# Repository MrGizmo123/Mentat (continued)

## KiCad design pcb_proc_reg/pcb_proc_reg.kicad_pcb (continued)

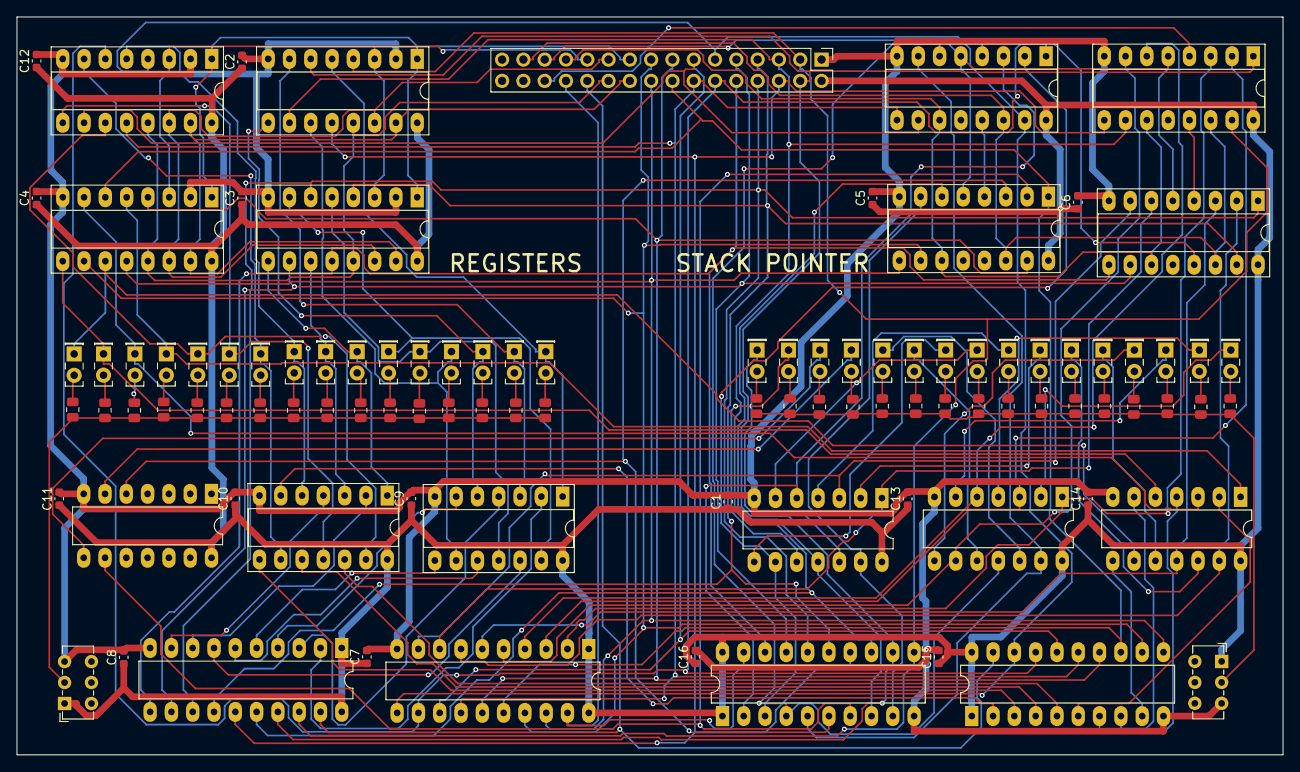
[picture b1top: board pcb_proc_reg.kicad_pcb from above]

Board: 2 copper layers, 151.0 x 88.0 mm, 101 parts (0 on the bottom side), 130 nets.

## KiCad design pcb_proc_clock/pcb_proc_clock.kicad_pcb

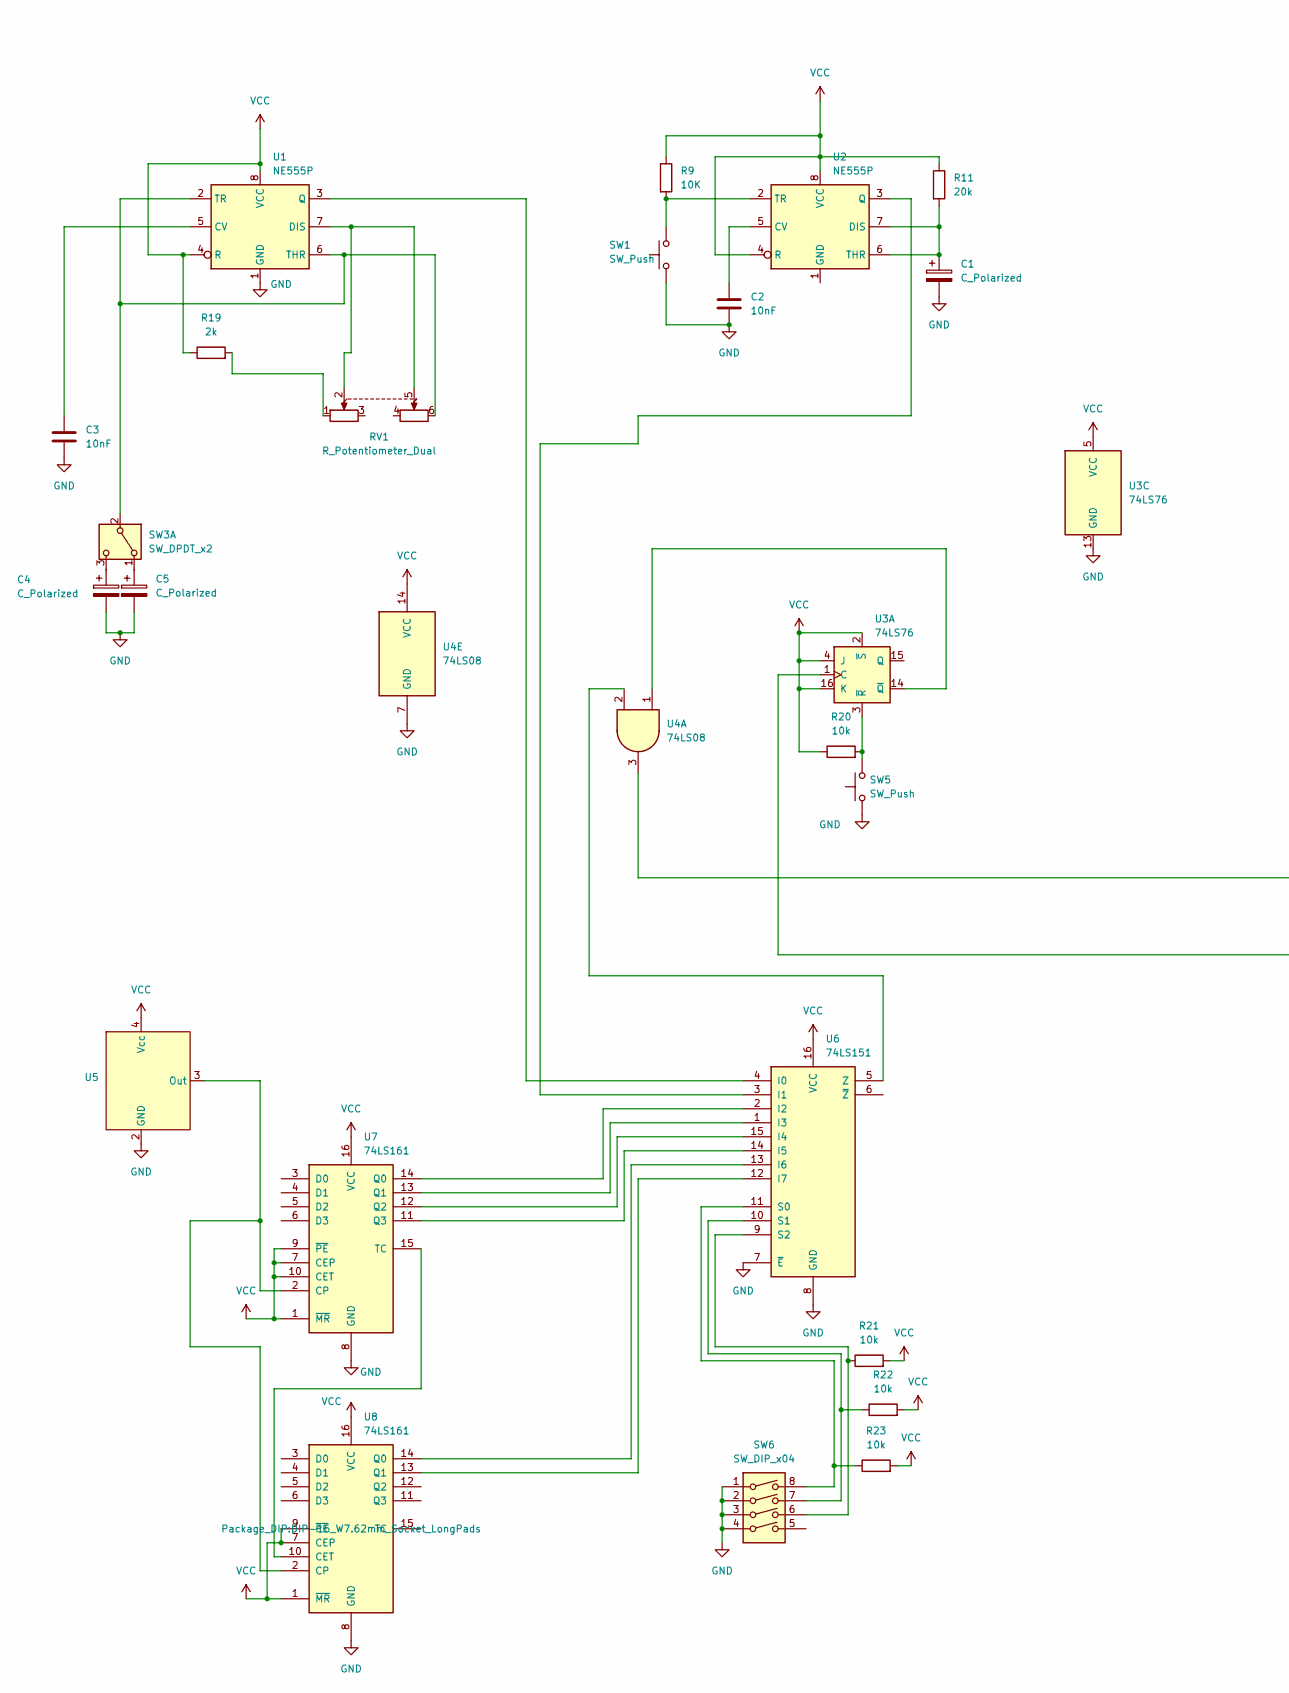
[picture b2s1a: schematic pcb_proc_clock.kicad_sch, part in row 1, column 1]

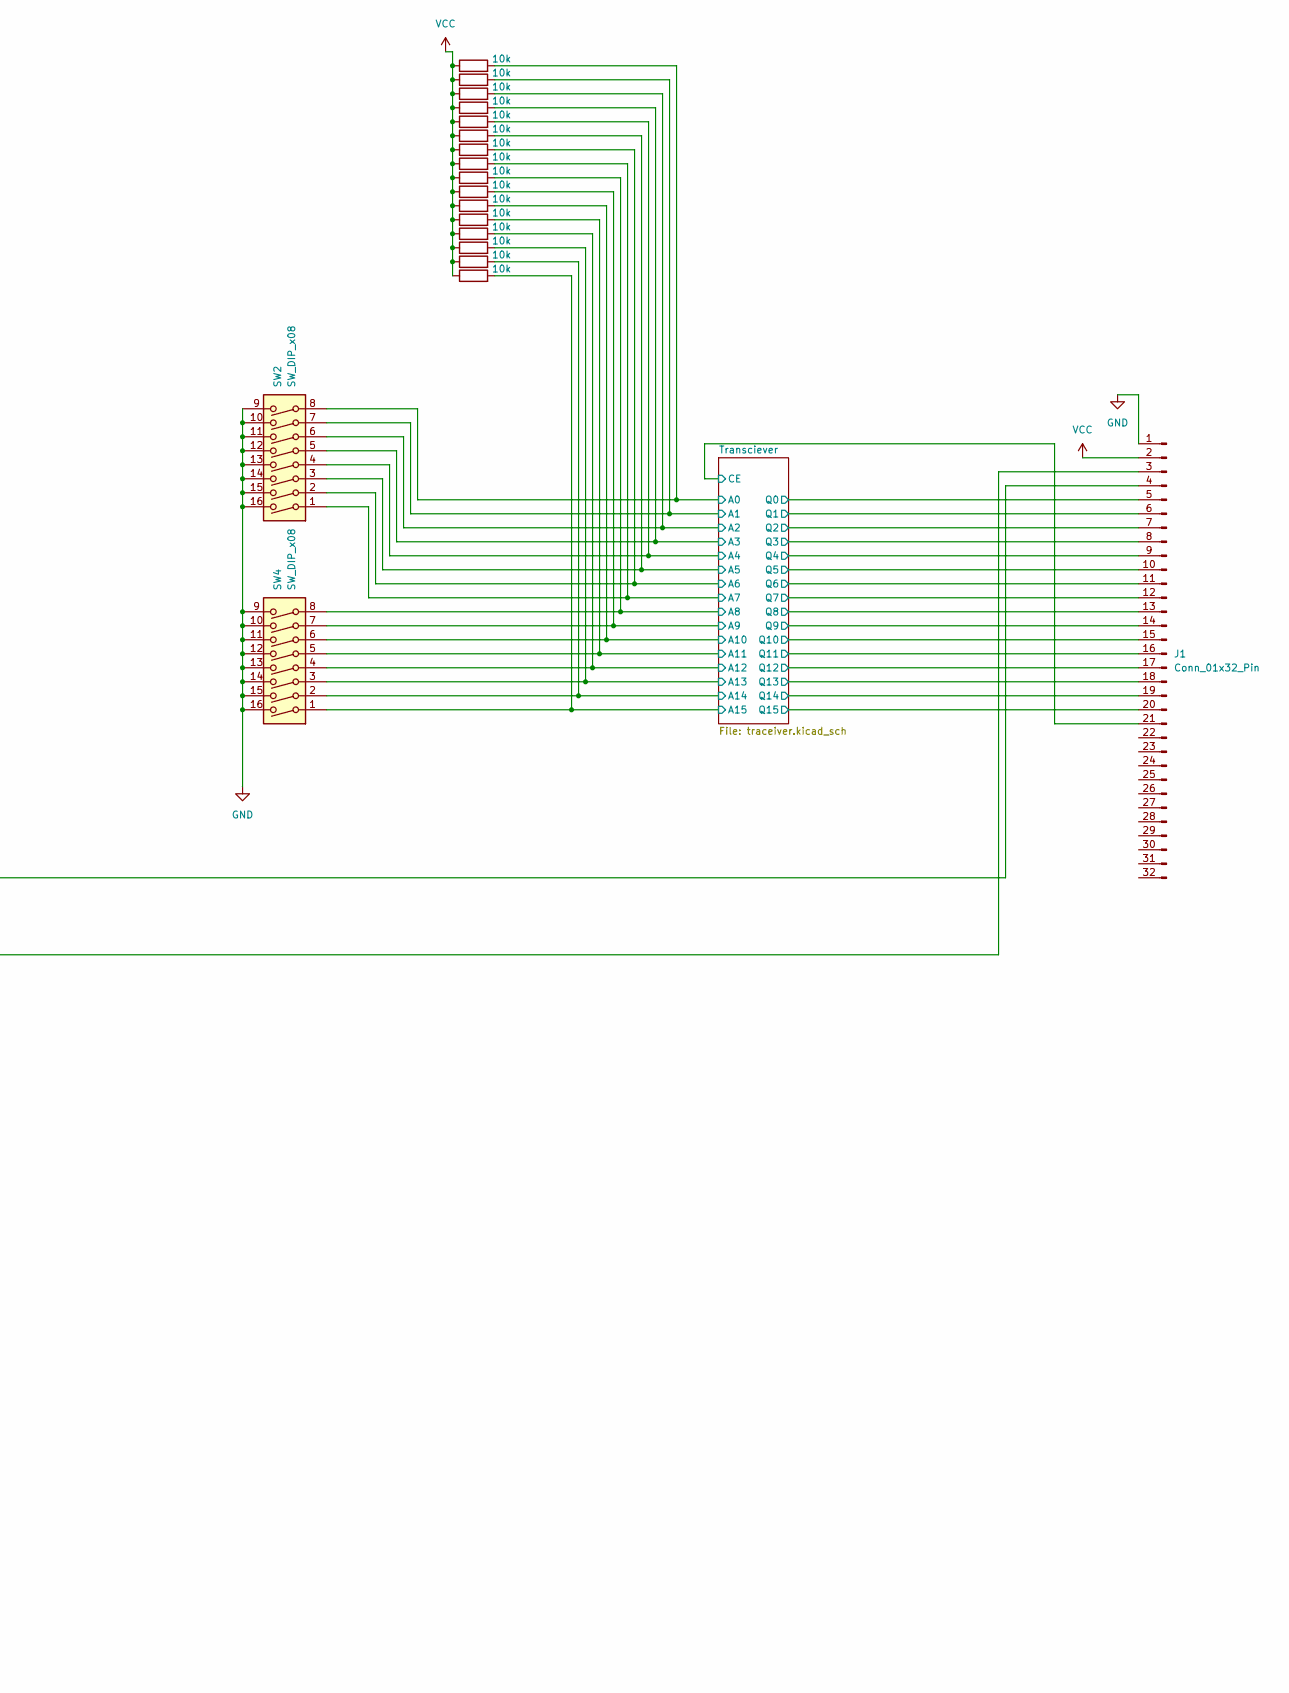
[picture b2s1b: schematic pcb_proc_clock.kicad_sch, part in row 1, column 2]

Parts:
C1, C4, C5: C_Polarized; CP_Radial_D4.0mm_P1.50mm
C2, C3: 10nF; C_Disc_D3.0mm_W1.6mm_P2.50mm
J1: Conn_01x32_Pin; PinHeader_2x16_P2.54mm_Vertical
R1, R2, R3, R4, R5, R6, R7, R8, R10, R12, R13, R14, R15, R16, R17, R18, R20, R21, R22, R23: 10k; R_0805_2012Metric
R9: 10K; R_0805_2012Metric
R11: 20k; R_0805_2012Metric
R19: 2k; R_0805_2012Metric
RV1: R_Potentiometer_Dual; Potentiometer_Alps_RK163_Dual_Horizontal
SW1, SW5: SW_Push; SW_PUSH_6mm
SW2, SW4: SW_DIP_x08; SW_DIP_SPSTx08_Slide_9.78x22.5mm_W7.62mm_P2.54mm
SW3: SW_DPDT_x2; SW_CK_JS202011CQN_DPDT_Straight
SW6: SW_DIP_x04; DIP-8_W7.62mm_LongPads
U1, U2: NE555P; DIP-8_W7.62mm_Socket_LongPads
U3: 74LS76; DIP-16_W7.62mm_Socket_LongPads
U4: 74LS08; DIP-14_W7.62mm_Socket_LongPads
U5: MCO-1510A
U6: 74LS151; DIP-16_W7.62mm_Socket_LongPads
U7, U8: 74LS161; DIP-16_W7.62mm_Socket_LongPads

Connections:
/Transciever/A0: R1.2, SW2.8; also elsewhere on the board
/Transciever/A1: R2.2, SW2.7; also elsewhere on the board
/Transciever/A2: R3.2, SW2.6; also elsewhere on the board
/Transciever/A3: R4.2, SW2.5; also elsewhere on the board
/Transciever/A4: R5.2, SW2.4; also elsewhere on the board
/Transciever/A5: R6.2, SW2.3; also elsewhere on the board
/Transciever/A6: R7.2, SW2.2; also elsewhere on the board
/Transciever/A7: R8.2, SW2.1; also elsewhere on the board
/Transciever/A8: R10.2, SW4.8; also elsewhere on the board
/Transciever/A9: R12.2, SW4.7; also elsewhere on the board
/Transciever/A10: R13.2, SW4.6; also elsewhere on the board
/Transciever/A11: R14.2, SW4.5; also elsewhere on the board
/Transciever/A12: R15.2, SW4.4; also elsewhere on the board
/Transciever/A13: R16.2, SW4.3; also elsewhere on the board
/Transciever/A14: R17.2, SW4.2; also elsewhere on the board
/Transciever/A15: R18.2, SW4.1; also elsewhere on the board
/Transciever/CE: J1.21; also elsewhere on the board
/Transciever/Q0: J1.5; also elsewhere on the board
/Transciever/Q1: J1.6; also elsewhere on the board
/Transciever/Q2: J1.7; also elsewhere on the board
/Transciever/Q3: J1.8; also elsewhere on the board
/Transciever/Q4: J1.9; also elsewhere on the board
/Transciever/Q5: J1.10; also elsewhere on the board
/Transciever/Q6: J1.11; also elsewhere on the board
/Transciever/Q7: J1.12; also elsewhere on the board
/Transciever/Q8: J1.13; also elsewhere on the board
/Transciever/Q9: J1.14; also elsewhere on the board
/Transciever/Q10: J1.15; also elsewhere on the board
/Transciever/Q11: J1.16; also elsewhere on the board
/Transciever/Q12: J1.17; also elsewhere on the board
/Transciever/Q13: J1.18; also elsewhere on the board
/Transciever/Q14: J1.19; also elsewhere on the board
/Transciever/Q15: J1.20; also elsewhere on the board
GND: C1.2, C2.2, C3.2, C4.2, C5.2, J1.1, SW1.1, SW2.9, SW2.10, SW2.11, SW2.12, SW2.13, SW2.14, SW2.15, SW2.16, SW4.9, SW4.10, SW4.11, SW4.12, SW4.13, SW4.14, SW4.15, SW4.16, SW5.1, SW6.1, SW6.2, SW6.3, SW6.4, U1.1 (GND), U3.13 (GND), U4.7 (GND), U5.2 (GND), U6.7 (~E), U6.8 (GND), U7.8 (GND), U8.8 (GND); also elsewhere on the board
unnamed: J1.3, U3.1 (C)
unnamed: J1.4, U4.3
unnamed: R19.2, RV1.1
unnamed: C5.1, SW3.1 (A)
unnamed: RV1.6, SW3.2 (B), U1.2 (TR), U1.6 (THR)
unnamed: C4.1, SW3.3 (C)
unnamed: C3.1, U1.5 (CV)
unnamed: RV1.2, RV1.5, U1.7 (DIS)
unnamed: U1.3 (Q), U6.4 (I0)
unnamed: C2.1, U2.5 (CV)
unnamed: C1.1, R11.2, U2.6 (THR), U2.7 (DIS)
unnamed: U2.3 (Q), U6.3 (I1)
unnamed: R9.2, SW1.2, U2.2 (TR)
unnamed: U3.14 (~Q), U4.1
unnamed: R20.2, SW5.2, U3.3 (~R)
unnamed: U5.3 (Out), U7.2 (CP), U8.2 (CP)
unnamed: U6.2 (I2), U7.14 (Q0)
unnamed: U6.1 (I3), U7.13 (Q1)
unnamed: U6.15 (I4), U7.12 (Q2)
unnamed: U6.14 (I5), U7.11 (Q3)
unnamed: U6.13 (I6), U8.14 (Q0)
unnamed: U6.12 (I7), U8.13 (Q1)
unnamed: R23.1, SW6.8, U6.11 (S0)
unnamed: R22.1, SW6.7, U6.10 (S1)
unnamed: R21.1, SW6.6, U6.9 (S2)
unnamed: U4.2, U6.5 (Z)
unnamed: U7.15 (TC), U8.10 (CET)
VCC: J1.2, R1.1, R2.1, R3.1, R4.1, R5.1, R6.1, R7.1, R8.1, R9.1, R10.1, R11.1, R12.1, R13.1, R14.1, R15.1, R16.1, R17.1, R18.1, R19.1, R20.1, R21.2, R22.2, R23.2, U1.4 (R), U1.8 (VCC), U2.4 (R), U2.8 (VCC), U3.2 (~S), U3.4 (J), U3.5 (VCC), U3.16 (K), U4.14 (VCC), U5.4 (Vcc), U6.16 (VCC), U7.1 (~MR), U7.7 (CEP), U7.9 (~PE), U7.10 (CET), U7.16 (VCC), U8.1 (~MR), U8.7 (CEP), U8.9 (~PE), U8.16 (VCC); also elsewhere on the board

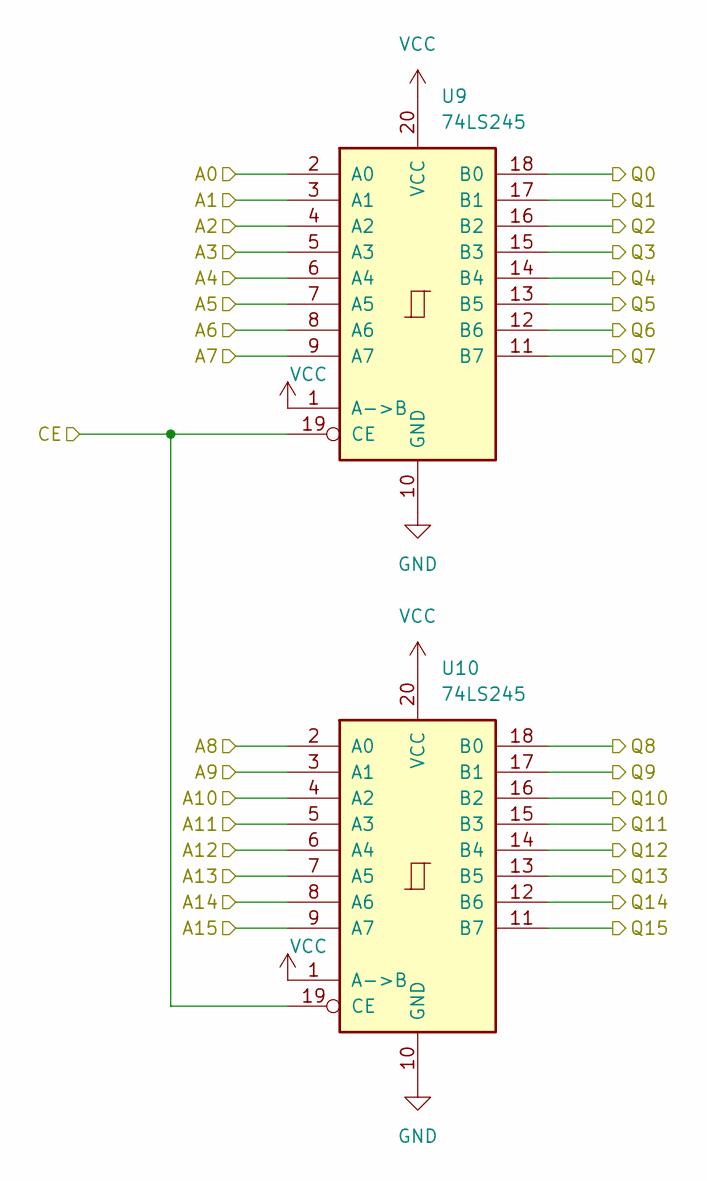
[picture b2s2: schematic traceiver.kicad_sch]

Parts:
U9, U10: 74LS245; DIP-20_W7.62mm_LongPads

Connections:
/Transciever/A0: U9.2 (A0); also elsewhere on the board
/Transciever/A1: U9.3 (A1); also elsewhere on the board
/Transciever/A2: U9.4 (A2); also elsewhere on the board
/Transciever/A3: U9.5 (A3); also elsewhere on the board
/Transciever/A4: U9.6 (A4); also elsewhere on the board
/Transciever/A5: U9.7 (A5); also elsewhere on the board
/Transciever/A6: U9.8 (A6); also elsewhere on the board
/Transciever/A7: U9.9 (A7); also elsewhere on the board
/Transciever/A8: U10.2 (A0); also elsewhere on the board
/Transciever/A9: U10.3 (A1); also elsewhere on the board
/Transciever/A10: U10.4 (A2); also elsewhere on the board
/Transciever/A11: U10.5 (A3); also elsewhere on the board
/Transciever/A12: U10.6 (A4); also elsewhere on the board
/Transciever/A13: U10.7 (A5); also elsewhere on the board
/Transciever/A14: U10.8 (A6); also elsewhere on the board
/Transciever/A15: U10.9 (A7); also elsewhere on the board
/Transciever/CE: U9.19 (CE), U10.19 (CE); also elsewhere on the board
/Transciever/Q0: U9.18 (B0); also elsewhere on the board
/Transciever/Q1: U9.17 (B1); also elsewhere on the board
/Transciever/Q2: U9.16 (B2); also elsewhere on the board
/Transciever/Q3: U9.15 (B3); also elsewhere on the board
/Transciever/Q4: U9.14 (B4); also elsewhere on the board
/Transciever/Q5: U9.13 (B5); also elsewhere on the board
/Transciever/Q6: U9.12 (B6); also elsewhere on the board
/Transciever/Q7: U9.11 (B7); also elsewhere on the board
/Transciever/Q8: U10.18 (B0); also elsewhere on the board
/Transciever/Q9: U10.17 (B1); also elsewhere on the board
/Transciever/Q10: U10.16 (B2); also elsewhere on the board
/Transciever/Q11: U10.15 (B3); also elsewhere on the board
/Transciever/Q12: U10.14 (B4); also elsewhere on the board
/Transciever/Q13: U10.13 (B5); also elsewhere on the board
/Transciever/Q14: U10.12 (B6); also elsewhere on the board
/Transciever/Q15: U10.11 (B7); also elsewhere on the board
GND: U9.10 (GND), U10.10 (GND); also elsewhere on the board
VCC: U9.1 (A->B), U9.20 (VCC), U10.1 (A->B), U10.20 (VCC); also elsewhere on the board

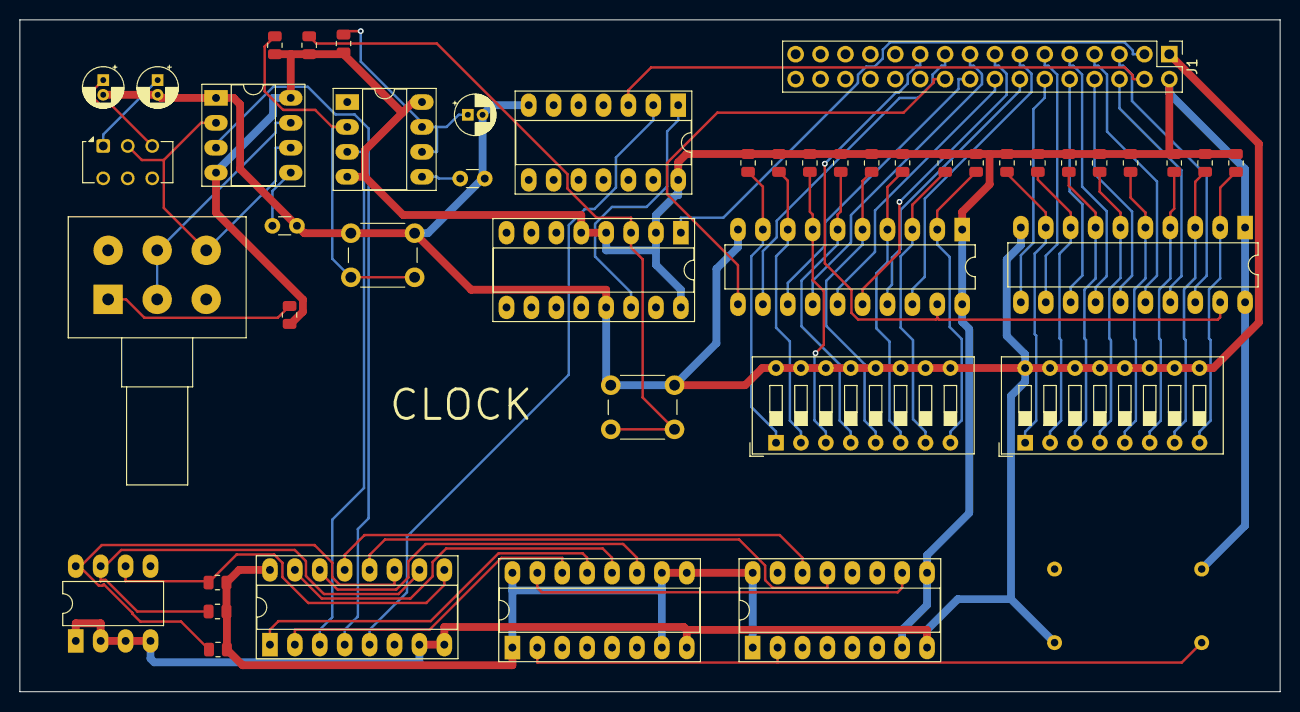
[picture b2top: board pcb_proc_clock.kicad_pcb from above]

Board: 2 copper layers, 128.5 x 68.5 mm, 46 parts (0 on the bottom side), 62 nets.

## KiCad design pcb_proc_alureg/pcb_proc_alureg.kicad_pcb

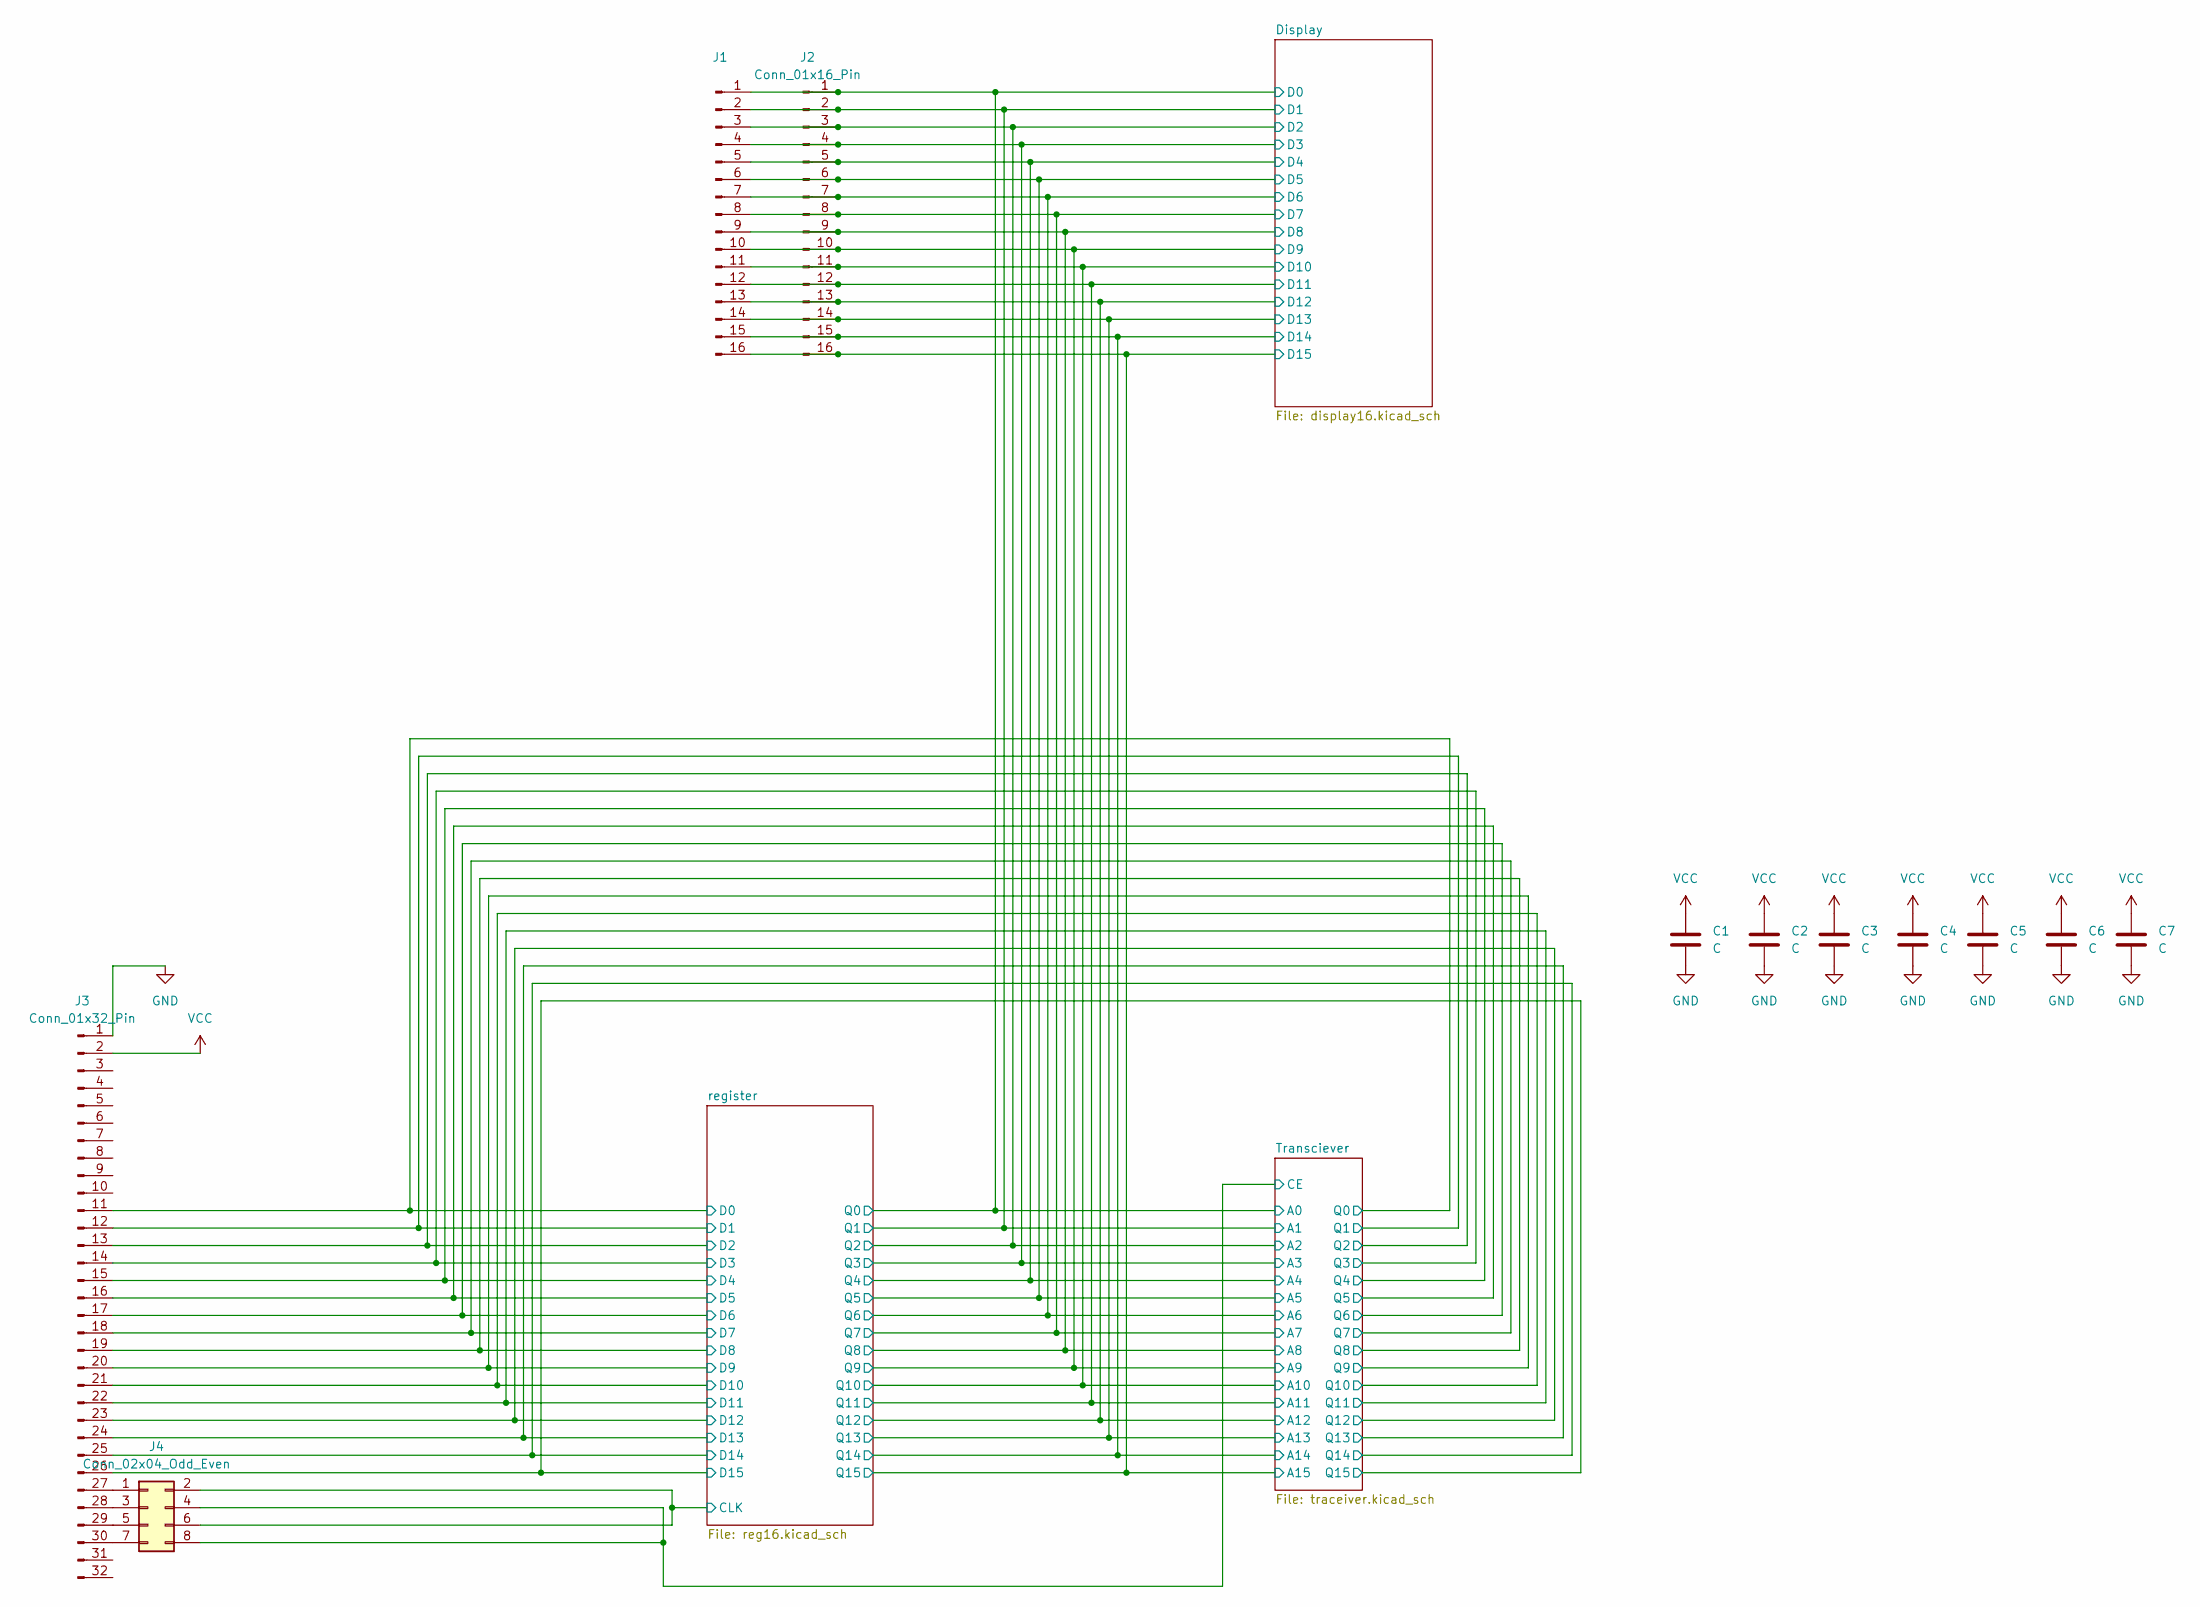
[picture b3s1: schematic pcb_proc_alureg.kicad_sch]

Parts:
C1, C2, C3, C4, C5, C6, C7: C; C_0805_2012Metric
J1, J2: Conn_01x16_Pin; PinSocket_1x16_P2.54mm_Vertical
J3: Conn_01x32_Pin; PinHeader_1x32_P2.54mm_Horizontal
J4: Conn_02x04_Odd_Even; PinSocket_2x04_P2.54mm_Vertical

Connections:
/Display/D0: J1.1, J2.1; also elsewhere on the board
/Display/D1: J1.2, J2.2; also elsewhere on the board
/Display/D2: J1.3, J2.3; also elsewhere on the board
/Display/D3: J1.4, J2.4; also elsewhere on the board
/Display/D4: J1.5, J2.5; also elsewhere on the board
/Display/D5: J1.6, J2.6; also elsewhere on the board
/Display/D6: J1.7, J2.7; also elsewhere on the board
/Display/D7: J1.8, J2.8; also elsewhere on the board
/Display/D8: J1.9, J2.9; also elsewhere on the board
/Display/D9: J1.10, J2.10; also elsewhere on the board
/Display/D10: J1.11, J2.11; also elsewhere on the board
/Display/D11: J1.12, J2.12; also elsewhere on the board
/Display/D12: J1.13, J2.13; also elsewhere on the board
/Display/D13: J1.14, J2.14; also elsewhere on the board
/Display/D14: J1.15, J2.15; also elsewhere on the board
/Display/D15: J1.16, J2.16; also elsewhere on the board
/Transciever/CE: J4.4, J4.8; also elsewhere on the board
/Transciever/Q0: J3.11; also elsewhere on the board
/Transciever/Q1: J3.12; also elsewhere on the board
/Transciever/Q2: J3.13; also elsewhere on the board
/Transciever/Q3: J3.14; also elsewhere on the board
/Transciever/Q4: J3.15; also elsewhere on the board
/Transciever/Q5: J3.16; also elsewhere on the board
/Transciever/Q6: J3.17; also elsewhere on the board
/Transciever/Q7: J3.18; also elsewhere on the board
/Transciever/Q8: J3.19; also elsewhere on the board
/Transciever/Q9: J3.20; also elsewhere on the board
/Transciever/Q10: J3.21; also elsewhere on the board
/Transciever/Q11: J3.22; also elsewhere on the board
/Transciever/Q12: J3.23; also elsewhere on the board
/Transciever/Q13: J3.24; also elsewhere on the board
/Transciever/Q14: J3.25; also elsewhere on the board
/Transciever/Q15: J3.26; also elsewhere on the board
/register/CLK: J4.2, J4.6; also elsewhere on the board
GND: C1.2, C2.2, C3.2, C4.2, C5.2, C6.2, C7.2, J3.1; also elsewhere on the board
unnamed: J3.27, J4.1
unnamed: J3.28, J4.3
unnamed: J3.29, J4.5
unnamed: J3.30, J4.7
VCC: C1.1, C2.1, C3.1, C4.1, C5.1, C6.1, C7.1, J3.2; also elsewhere on the board

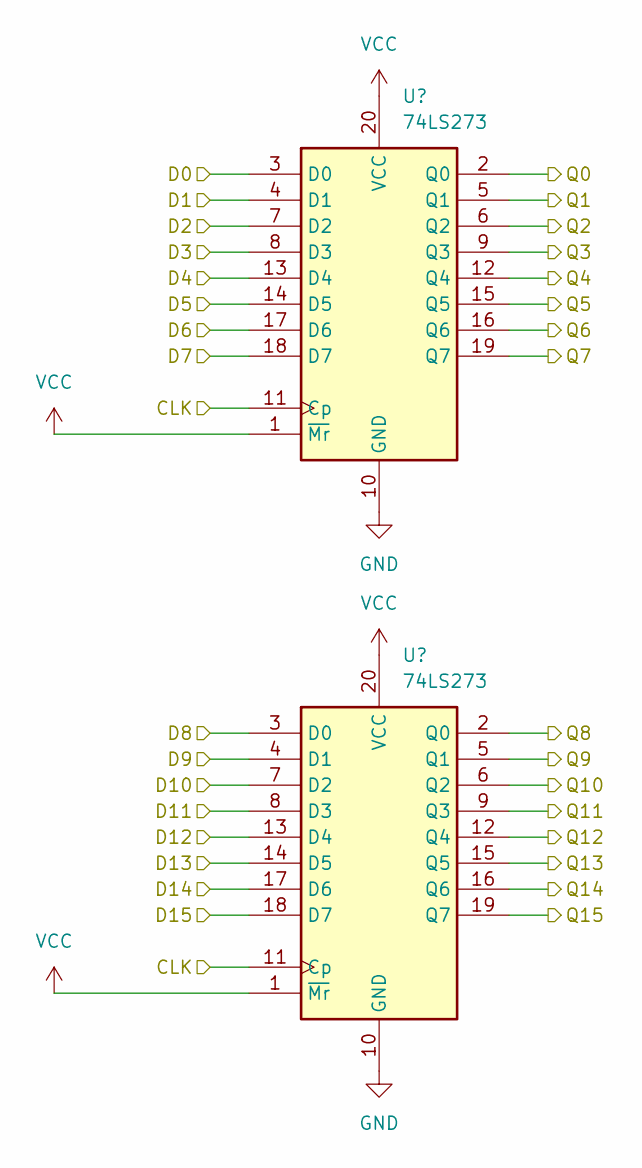
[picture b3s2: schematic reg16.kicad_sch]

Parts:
U4, U5: 74LS273; DIP-20_W7.62mm_Socket_LongPads

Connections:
/Display/D0: U4.2 (Q0); also elsewhere on the board
/Display/D1: U4.5 (Q1); also elsewhere on the board
/Display/D2: U4.6 (Q2); also elsewhere on the board
/Display/D3: U4.9 (Q3); also elsewhere on the board
/Display/D4: U4.12 (Q4); also elsewhere on the board
/Display/D5: U4.15 (Q5); also elsewhere on the board
/Display/D6: U4.16 (Q6); also elsewhere on the board
/Display/D7: U4.19 (Q7); also elsewhere on the board
/Display/D8: U5.2 (Q0); also elsewhere on the board
/Display/D9: U5.5 (Q1); also elsewhere on the board
/Display/D10: U5.6 (Q2); also elsewhere on the board
/Display/D11: U5.9 (Q3); also elsewhere on the board
/Display/D12: U5.12 (Q4); also elsewhere on the board
/Display/D13: U5.15 (Q5); also elsewhere on the board
/Display/D14: U5.16 (Q6); also elsewhere on the board
/Display/D15: U5.19 (Q7); also elsewhere on the board
/Transciever/Q0: U4.3 (D0); also elsewhere on the board
/Transciever/Q1: U4.4 (D1); also elsewhere on the board
/Transciever/Q2: U4.7 (D2); also elsewhere on the board
/Transciever/Q3: U4.8 (D3); also elsewhere on the board
/Transciever/Q4: U4.13 (D4); also elsewhere on the board
/Transciever/Q5: U4.14 (D5); also elsewhere on the board
/Transciever/Q6: U4.17 (D6); also elsewhere on the board
/Transciever/Q7: U4.18 (D7); also elsewhere on the board
/Transciever/Q8: U5.3 (D0); also elsewhere on the board
/Transciever/Q9: U5.4 (D1); also elsewhere on the board
/Transciever/Q10: U5.7 (D2); also elsewhere on the board
/Transciever/Q11: U5.8 (D3); also elsewhere on the board
/Transciever/Q12: U5.13 (D4); also elsewhere on the board
/Transciever/Q13: U5.14 (D5); also elsewhere on the board
/Transciever/Q14: U5.17 (D6); also elsewhere on the board
/Transciever/Q15: U5.18 (D7); also elsewhere on the board
/register/CLK: U4.11 (Cp), U5.11 (Cp); also elsewhere on the board
GND: U4.10 (GND), U5.10 (GND); also elsewhere on the board
VCC: U4.1 (~Mr), U4.20 (VCC), U5.1 (~Mr), U5.20 (VCC); also elsewhere on the board

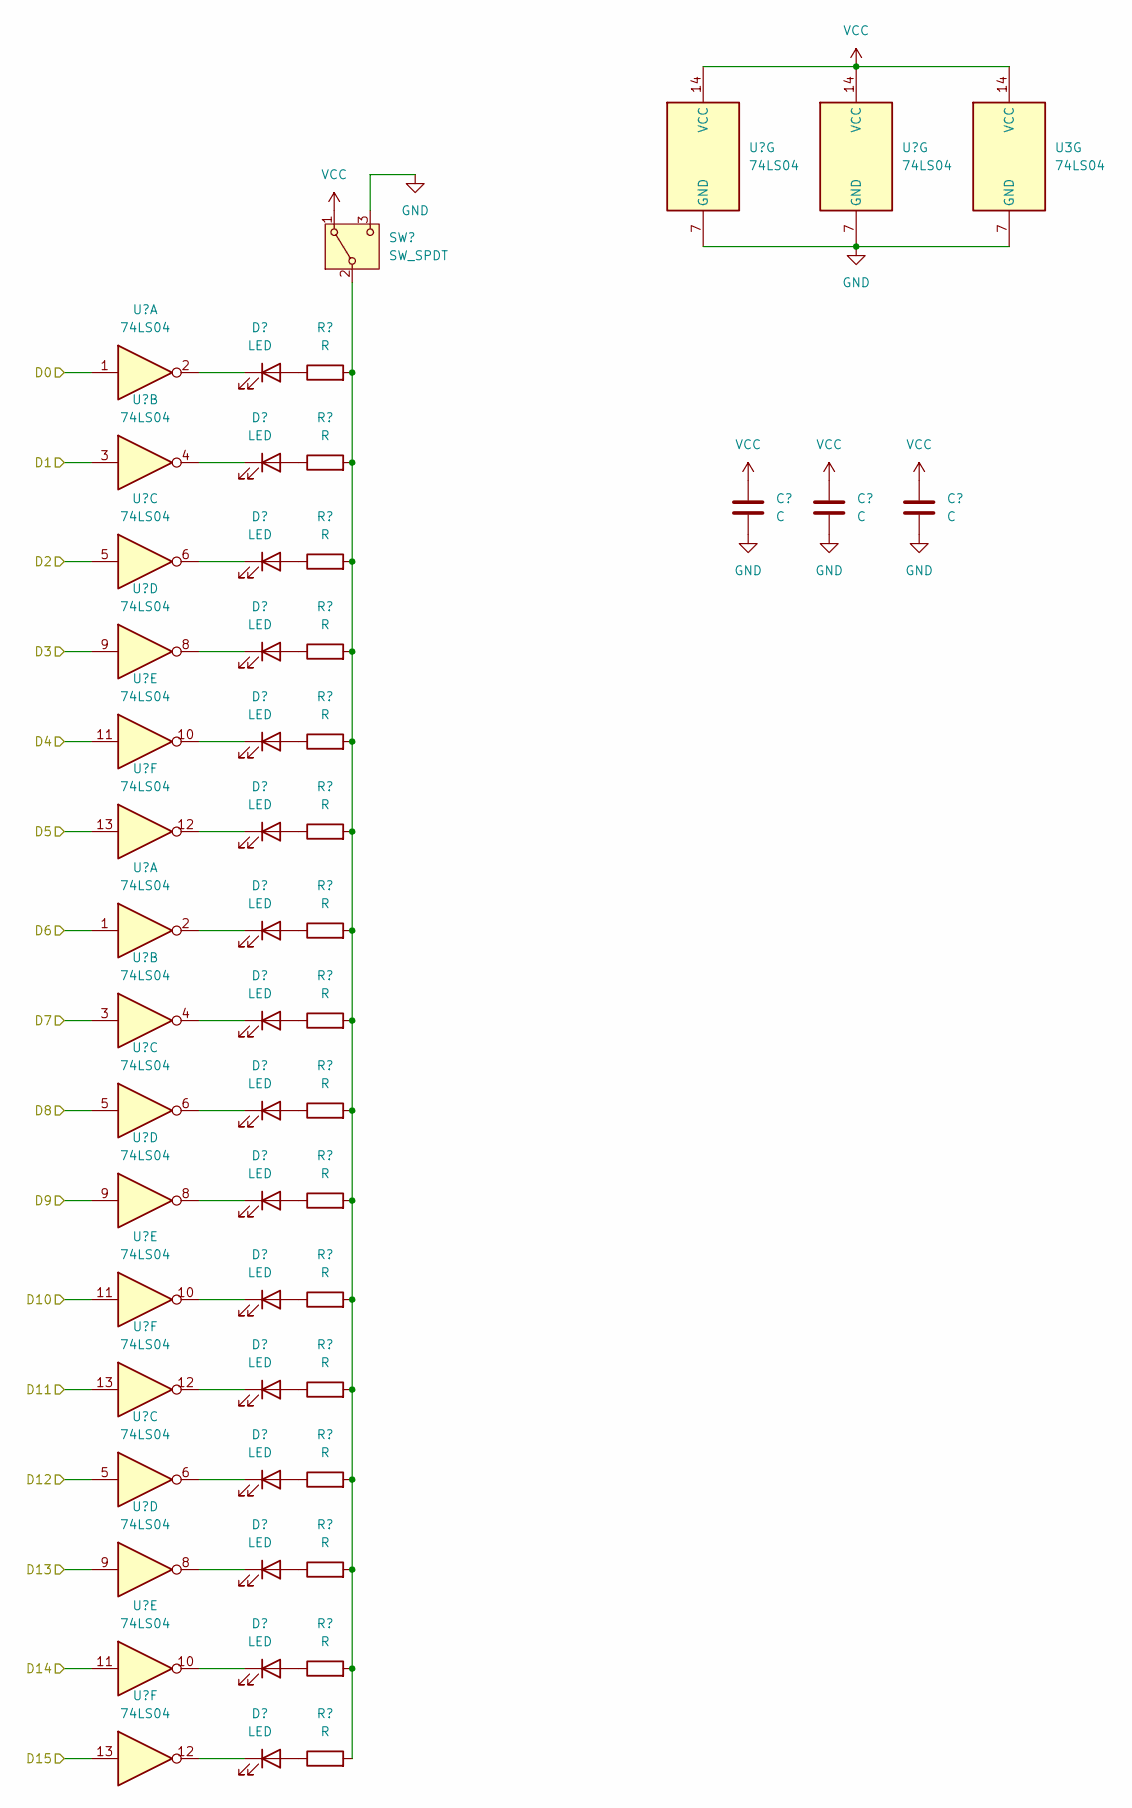
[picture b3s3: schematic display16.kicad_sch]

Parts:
C8, C9, C10: C; C_0805_2012Metric
D1, D2, D3, D4, D5, D6, D7, D8, D9, D10, D11, D12, D13, D14, D15, D16: LED; LED_Rectangular_W5.0mm_H2.0mm
R1, R2, R3, R4, R5, R6, R7, R8, R9, R10, R11, R12, R13, R14, R15, R16: R; R_0805_2012Metric
SW1: SW_SPDT; SW_E-Switch_EG1271_SPDT
U1: 74LS04; DIP-14_W7.62mm_Socket_LongPads
U2, U3: 74LS04; DIP-14_W7.62mm_LongPads

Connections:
/Display/D0: U1.1; also elsewhere on the board
/Display/D1: U1.3; also elsewhere on the board
/Display/D2: U1.5; also elsewhere on the board
/Display/D3: U1.9; also elsewhere on the board
/Display/D4: U1.11; also elsewhere on the board
/Display/D5: U1.13; also elsewhere on the board
/Display/D6: U2.1; also elsewhere on the board
/Display/D7: U2.3; also elsewhere on the board
/Display/D8: U2.5; also elsewhere on the board
/Display/D9: U2.9; also elsewhere on the board
/Display/D10: U2.11; also elsewhere on the board
/Display/D11: U2.13; also elsewhere on the board
/Display/D12: U3.5; also elsewhere on the board
/Display/D13: U3.9; also elsewhere on the board
/Display/D14: U3.11; also elsewhere on the board
/Display/D15: U3.13; also elsewhere on the board
GND: C8.2, C9.2, C10.2, SW1.3 (C), U1.7 (GND), U2.7 (GND), U3.7 (GND); also elsewhere on the board
unnamed: D1.2 (A), R1.1
unnamed: D1.1 (K), U1.2
unnamed: D2.2 (A), R2.1
unnamed: D2.1 (K), U1.4
unnamed: D3.2 (A), R3.1
unnamed: D3.1 (K), U1.6
unnamed: D4.2 (A), R4.1
unnamed: D4.1 (K), U1.8
unnamed: D5.2 (A), R5.1
unnamed: D5.1 (K), U1.10
unnamed: D6.2 (A), R6.1
unnamed: D6.1 (K), U1.12
unnamed: D7.2 (A), R7.1
unnamed: D7.1 (K), U2.2
unnamed: D8.2 (A), R8.1
unnamed: D8.1 (K), U2.4
unnamed: D9.2 (A), R9.1
unnamed: D9.1 (K), U2.6
unnamed: D10.2 (A), R10.1
unnamed: D10.1 (K), U2.8
unnamed: D11.2 (A), R11.1
unnamed: D11.1 (K), U2.10
unnamed: D12.2 (A), R12.1
unnamed: D12.1 (K), U2.12
unnamed: D13.2 (A), R13.1
unnamed: D13.1 (K), U3.6
unnamed: D14.2 (A), R14.1
unnamed: D14.1 (K), U3.8
unnamed: D15.2 (A), R15.1
unnamed: D15.1 (K), U3.10
unnamed: D16.2 (A), R16.1
unnamed: D16.1 (K), U3.12
unnamed: R1.2, R2.2, R3.2, R4.2, R5.2, R6.2, R7.2, R8.2, R9.2, R10.2, R11.2, R12.2, R13.2, R14.2, R15.2, R16.2, SW1.2 (B)
VCC: C8.1, C9.1, C10.1, SW1.1 (A), U1.14 (VCC), U2.14 (VCC), U3.14 (VCC); also elsewhere on the board
